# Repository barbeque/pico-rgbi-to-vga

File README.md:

# Pico RGBI to VGA
_(Name subject to change in future)_

## Current Status
Not working

TODO:
 - [ ] Hook up logic analyzer example to capture input video
 - [ ] Buffer input video into output
 - [ ] Test 4-bit colour output mode
 - [ ] Create multiple palettes and palette switch handler

## The Problem
Several old computers, such as the NEC PC-6001mkII, use an "RGB+I" output at TTL level (+5V.) It is becoming difficult to locate monitors which support this output. Modern displays, and I use the term loosely because the VGA port has virtually become extinct as I am writing this in 2022, use analogue RGB to convey a greater range of colours.

For some computers, such as the NEC PC-8801mkII and Sanyo MBC-555, there are only three digital pins: red, green, and blue. Combined, this makes 8 colours (2<sup>3</sup> = 8.) Later computers added an "intensity" pin, which essentially works as the equivalent of a Shift key for these colours, and expands the available colours to 15 (2<sup>4</sup> = 16, but "bright black" is still just black.) For instance, the PC-6001mkII will signal "bright red" as by setting the "red" and "intensity" pins to 5V and everything else to 0V. "White" would set all four pins to 5V.

## Current Status
The board is still *IN DEVELOPMENT*. Please do not use it unless you are willing to test with your machines, potentially write some code, and submit bug reports and feedback. There may be a risk of damage to your hardware or to the Pico if things go wrong.

## Compatibility
Here is a brief list of computers that are known to work with such a model, although they may require a custom cable made for this board:

 | Computer | Adapter configuration | Notes |
 |----------|-----------------------|-------|
 | NEC PC-6001mkII | Intensity: pin 3 | Not tested |
 | NEC PC-6001mkIISR | Intensity: pin 3 | Not tested |
 | NEC PC-6601 | Intensity: pin 3 | Not tested |
 | NEC PC-6601SR | Intensity: pin 3 | Not tested |
 | NEC PC-9801UV | Disable intensity | Not tested |
 | NEC PC-8001 | Disable intensity | Not tested |
 | NEC PC-8801mkII | Intensity *must* be disabled or it will pass +12V through and *damage the Pico*! | Not tested |
 | IBM CGA | Custom cable required | Not tested |
 | Sanyo MBC-550/MBC-555 | Disable intensity | Not tested |
 | Commodore C128 | Custom cable required | Not tested |
 | Fujitsu FM-7/FM-New7 | Disable intensity | Not tested; intensity may not be possible |
 | Fujitsu FM-77AV2 | Custom cable required | Not tested; intensity may not be possible |

Please submit a pull request if you have tested another computer, know of one to add to the list, or can contribute custom cable designs.

## Build Instructions
### Hardware
TODO

### Software
Refer to [the `firmware` directory](firmware/)'s README for build instructions.

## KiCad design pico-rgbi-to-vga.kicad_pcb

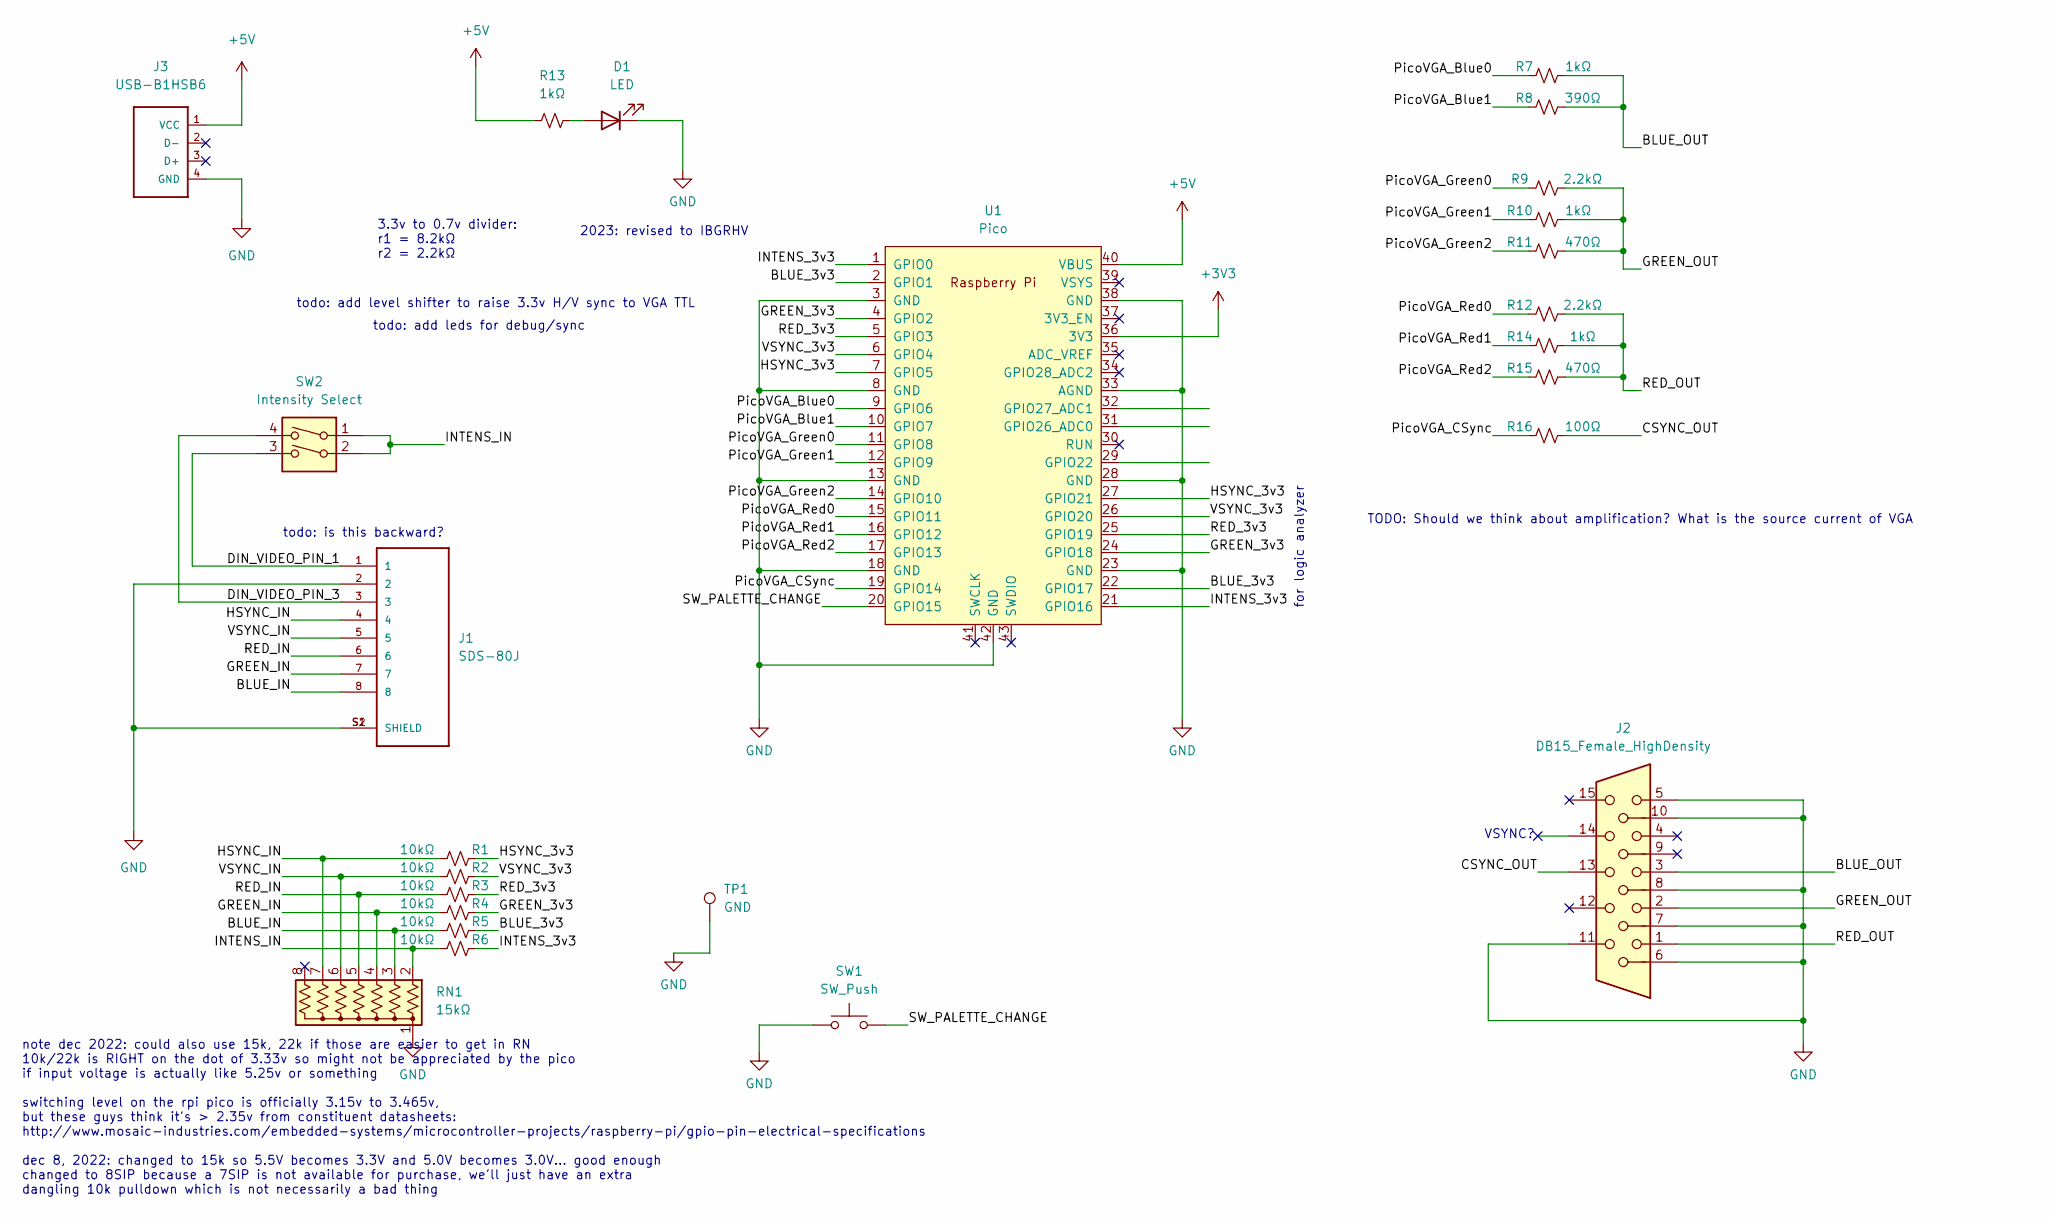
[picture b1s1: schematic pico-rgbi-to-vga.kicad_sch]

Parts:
D1: LED; LED_D3.0mm
J1: SDS-80J; CUI_SDS-80J
J2: DB15_Female_HighDensity; FIXED-1-1734530-1
J3: USB-B1HSB6; OST_USB-B1HSB6; DigiKey ED2983-ND
R1, R2, R3, R4, R5, R6: 10kΩ; R_0805_2012Metric_Pad1.20x1.40mm_HandSolder
R7, R10, R13, R14: 1kΩ; R_0805_2012Metric_Pad1.20x1.40mm_HandSolder
R8: 390Ω; R_0805_2012Metric_Pad1.20x1.40mm_HandSolder
R9, R12: 2.2kΩ; R_0805_2012Metric_Pad1.20x1.40mm_HandSolder
R11, R15: 470Ω; R_0805_2012Metric_Pad1.20x1.40mm_HandSolder
R16: 100Ω; R_0805_2012Metric_Pad1.20x1.40mm_HandSolder
RN1: 15kΩ; R_Array_SIP8
SW1: SW_Push; SW_PUSH_6mm
SW2: Intensity Select; SW_DIP_SPSTx02_Slide_6.7x6.64mm_W7.62mm_P2.54mm_LowProfile
TP1: GND; TestPoint_Loop_D2.54mm_Drill1.5mm_Beaded
U1: Pico; RPi_Pico_SMD_TH

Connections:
+3V3: U1.36 (3V3)
+5V: J3.1 (VCC), R13.1, U1.40 (VBUS)
/BLUE_3v3: R5.1, U1.2 (GPIO1), U1.22 (GPIO17)
/BLUE_IN: J1.8, R5.2, RN1.3 (R2)
/BLUE_OUT: J2.3, R7.2, R8.2
/CSYNC_OUT: J2.13, R16.2
/DIN_VIDEO_PIN_1: J1.1, SW2.3
/DIN_VIDEO_PIN_3: J1.3, SW2.4
/GREEN_3v3: R4.1, U1.4 (GPIO2), U1.24 (GPIO18)
/GREEN_IN: J1.7, R4.2, RN1.4 (R3)
/GREEN_OUT: J2.2, R9.2, R10.2, R11.2
/HSYNC_3v3: R1.1, U1.7 (GPIO5), U1.27 (GPIO21)
/HSYNC_IN: J1.4, R1.2, RN1.7 (R6)
/INTENS_3v3: R6.1, U1.1 (GPIO0), U1.21 (GPIO16)
/INTENS_IN: R6.2, RN1.2 (R1), SW2.1, SW2.2
/PicoVGA_Blue0: R7.1, U1.9 (GPIO6)
/PicoVGA_Blue1: R8.1, U1.10 (GPIO7)
/PicoVGA_CSync: R16.1, U1.19 (GPIO14)
/PicoVGA_Green0: R9.1, U1.11 (GPIO8)
/PicoVGA_Green1: R10.1, U1.12 (GPIO9)
/PicoVGA_Green2: R11.1, U1.14 (GPIO10)
/PicoVGA_Red0: R12.1, U1.15 (GPIO11)
/PicoVGA_Red1: R14.1, U1.16 (GPIO12)
/PicoVGA_Red2: R15.1, U1.17 (GPIO13)
/RED_3v3: R3.1, U1.5 (GPIO3), U1.25 (GPIO19)
/RED_IN: J1.6, R3.2, RN1.5 (R4)
/RED_OUT: J2.1, R12.2, R14.2, R15.2
/SW_PALETTE_CHANGE: SW1.2, U1.20 (GPIO15)
/VSYNC_3v3: R2.1, U1.6 (GPIO4), U1.26 (GPIO20)
/VSYNC_IN: J1.5, R2.2, RN1.6 (R5)
GND: D1.1 (K), J1.2, J1.S1 (SHIELD), J1.S2 (SHIELD), J2.5, J2.6, J2.7, J2.8, J2.10, J2.11, J3.4 (GND), RN1.1 (common), SW1.1, TP1.1, U1.3 (GND), U1.8 (GND), U1.13 (GND), U1.18 (GND), U1.23 (GND), U1.28 (GND), U1.33 (AGND), U1.38 (GND), U1.42 (GND)
unnamed: D1.2 (A), R13.2

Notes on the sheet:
TODO: Should we think about amplification? What is the source current of VGA
3.3v to 0.7v divider: r1 = 8.2kΩ r2 = 2.2kΩ
todo: is this backward?
2023: revised to IBGRHV
todo: add leds for debug/sync
VSYNC?
note dec 2022: could also use 15k, 22k if those are easier to get in RN 10k/22k is RIGHT on the dot of 3.33v so might not be appreciated by the pico if input voltage is actually like 5.25v or something switching level on the rpi pico is officially 3.15v to 3.465v, but these guys think it's > 2.35v 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
todo: add level shifter to raise 3.3v H/V sync to VGA TTL
for logic analyzer

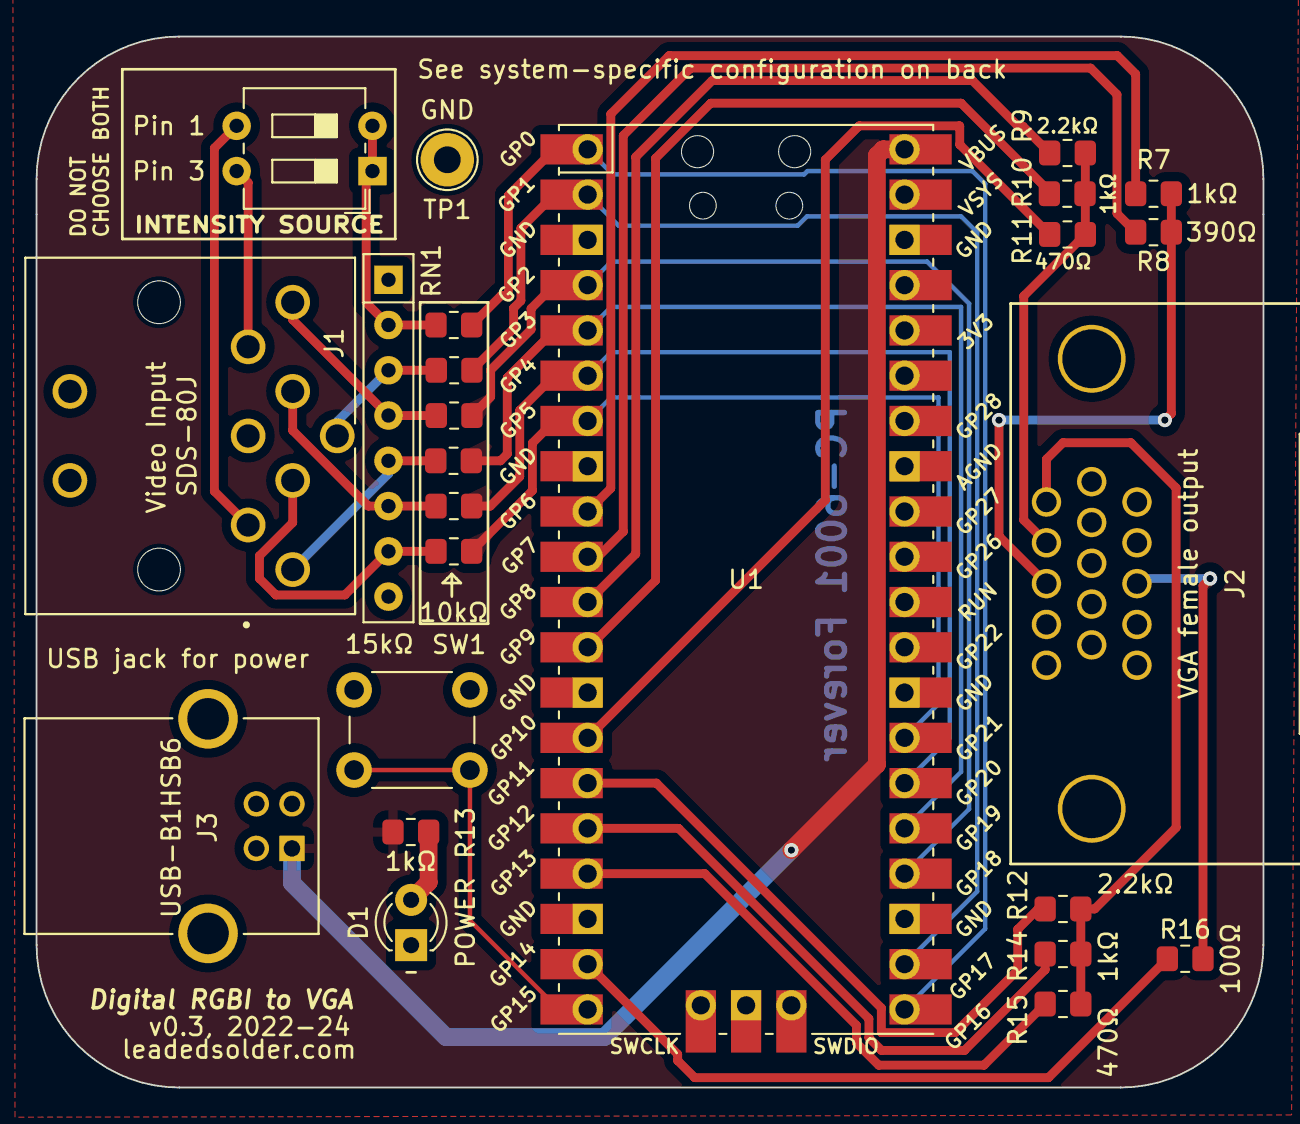
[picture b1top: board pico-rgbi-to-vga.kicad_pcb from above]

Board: 2 copper layers, 68.8 x 59.0 mm, 25 parts (0 on the bottom side), 31 nets.

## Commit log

2022-11-05 Sketchy rough-out
2022-11-05 Ground plane, bigger board
2022-11-05 Keepout
2022-11-17 Basic left-side implementation with voltage divider
2022-11-17 Power LED, output voltage divider
2022-11-17 Power plane
2022-11-17 Fully laid out, I think
2022-11-17 Palette toggle button
2022-11-17 V0.1 sent to Fab
2022-11-17 Use PicoVGA resistor ladder
2022-11-17 V0.2
2022-12-07 Change divider values
2022-12-07 Fix label
2022-12-07 Use 8SIP for Vdiv pulldown, 7SIP is not available
2022-12-11 Fix VGA output pins to use GPIOs that exist
2022-12-11 Add compatibility notes and cautions
2022-12-11 15-colour mode
2022-12-11 Source from raytracer
2022-12-11 A wordy CMake file
2022-12-11 A successful build
2022-12-12 README in case I come back to this later
2022-12-12 Change the sky colour
2022-12-12 Remove generated files
2022-12-12 Set up firmware in repository from PicoVGA example, but use cmake (#1)
    * Source from raytracer
    * A wordy CMake file
    * A successful build
    * README in case I come back to this later
    * Change the sky colour
    * Remove generated files
2022-12-12 Ignore pico_base
2022-12-26 Test drawing code
2022-12-27 Reduce layers to slightly lower RAM
2023-04-07 Link to Mac RPi Pico setup
2023-04-07 Fix PicoVGA path computation
2023-04-07 README updates
2023-04-07 Status
2023-04-08 KiCad7; reorder pins so HV won't get captured
2023-05-23 Rewired to be IBGRHV
2023-12-18 Doubts about DIN8 pinout
2024-06-03 Set heights for turbocase
2024-06-03 Prepare for turbocase
2024-12-04 Update to kicad 8
2024-12-13 Some captures from the Pico
2024-12-13 Fix boneheaded pinout mixup
2024-12-13 Get rid of the bad captures
2024-12-15 ignore plot files
2024-12-15 V0.3 prep, adding logic analyzer lines
2024-12-15 Plot v0.3

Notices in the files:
parts and their libraries:
Copyright 2016 Accelerated Designs. All rights reserved.
